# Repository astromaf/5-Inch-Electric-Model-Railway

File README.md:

# 5" Electric  Model Railway

Lovers of model railways have a wide collection of scales. One of the rarest are the 5-inch gauge. These machines are capable of taking several wagons full of visitors through an outdoor park. There are many different types, with steam being the most striking and representative.

I like to build things, and in this repository I leave useful material on the construction of my first machine, a very simple electrical model. I have done this project with my father, who is the person who has passed on my love for trains.

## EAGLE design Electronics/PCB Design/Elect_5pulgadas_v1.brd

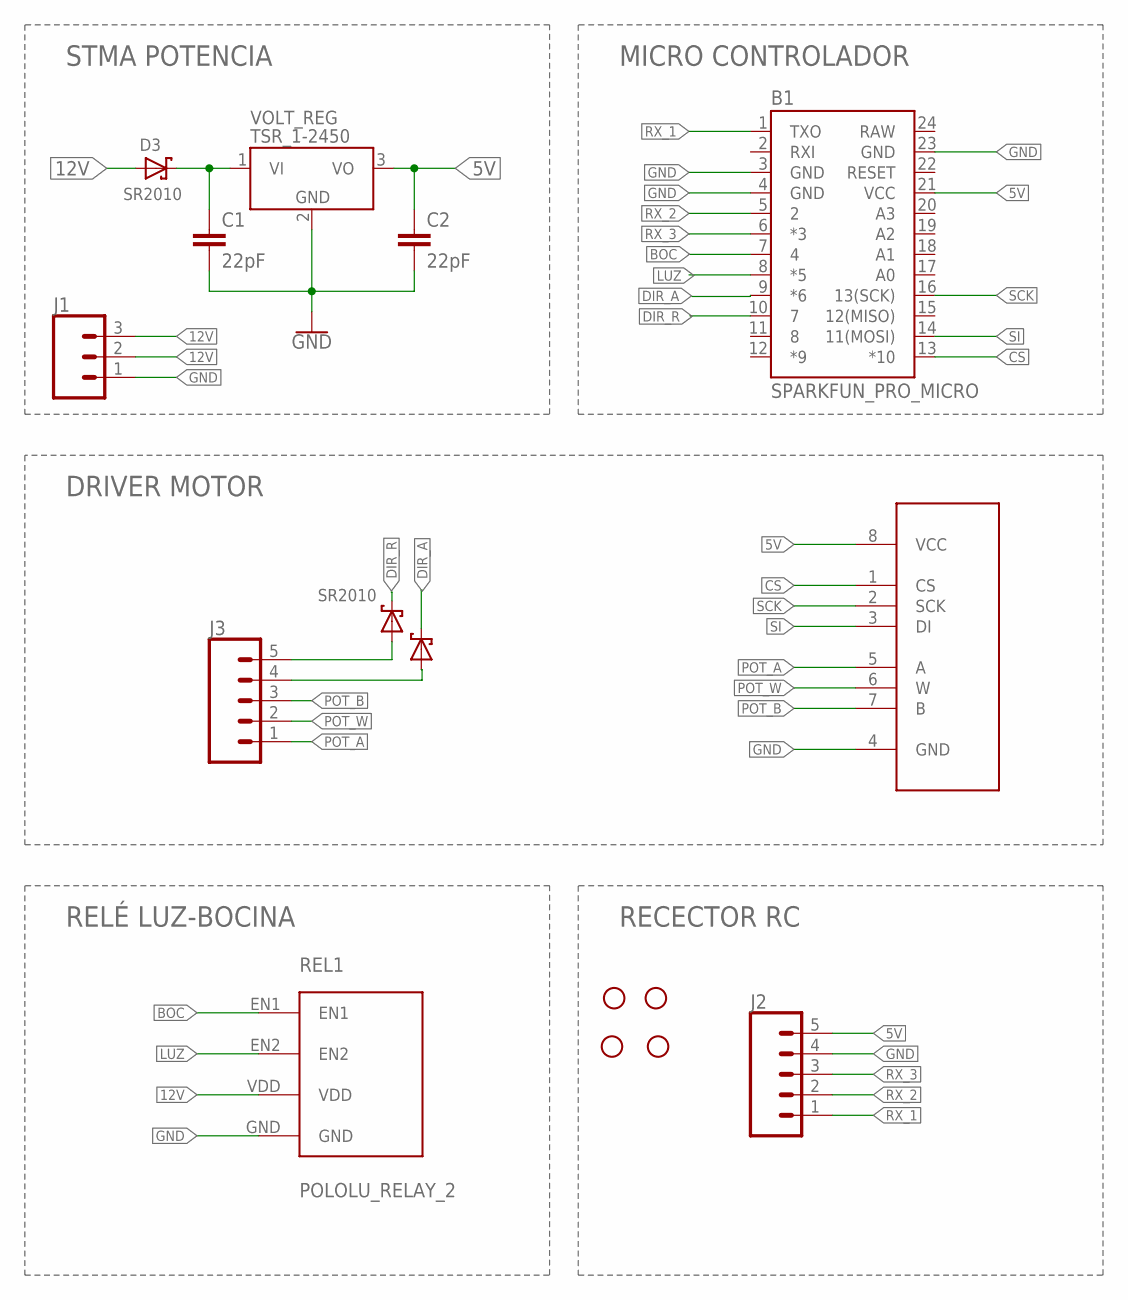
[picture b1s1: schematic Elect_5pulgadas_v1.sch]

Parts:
B1: SPARKFUN_PRO_MICRO
C1, C2: 22pF; CAP-PTH-SMALL-KIT
D1, D2, D3: SR2010; DO41-7.6
H1, H2, H3, H4: STAND-OFF
J1: CONN_03-SCREW-5MM; SCREWTERMINAL-5MM-3
J2, J3: CONN_05; 1X05
REL1: POLOLU_RELAY_2
U1: MCP41XXX; DIP08
VOLT_REG: TSR_1-2450; TSR-1

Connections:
5V: B1.21 (VCC), C2.1, J2.5, U1.8 (VCC), VOLT_REG.3 (VO)
12V: D3.A, J1.2, J1.3, REL1.VDD
BOC: B1.7 (4), REL1.EN1
CS: B1.13 (*10), U1.1 (CS)
DIR_A: B1.9 (*6), D1.C
DIR_R: B1.10 (7), D2.C
GND: B1.3 (GND), B1.4 (GND), B1.23 (GND), C1.2, C2.2, J1.1, J2.4, REL1.GND, U1.4 (GND), VOLT_REG.2 (GND)
LUZ: B1.8 (*5), REL1.EN2
unnamed: D1.A, J3.4
unnamed: D2.A, J3.5
POT_A: J3.1, U1.5 (A)
POT_B: J3.3, U1.7 (B)
POT_W: J3.2, U1.6 (W)
RAW: B1.24 (RAW)
RX_1: B1.1 (TXO), J2.1
RX_2: B1.5 (2), J2.2
RX_3: B1.6 (*3), J2.3
SCK: B1.16 (13(SCK)), U1.2 (SCK)
SI: B1.14 (11(MOSI)), U1.3 (DI)
VI: C1.1, D3.C, VOLT_REG.1 (VI)

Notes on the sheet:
STMA POTENCIA
RELÉ LUZ-BOCINA
DRIVER MOTOR
RECECTOR RC
MICRO CONTROLADOR

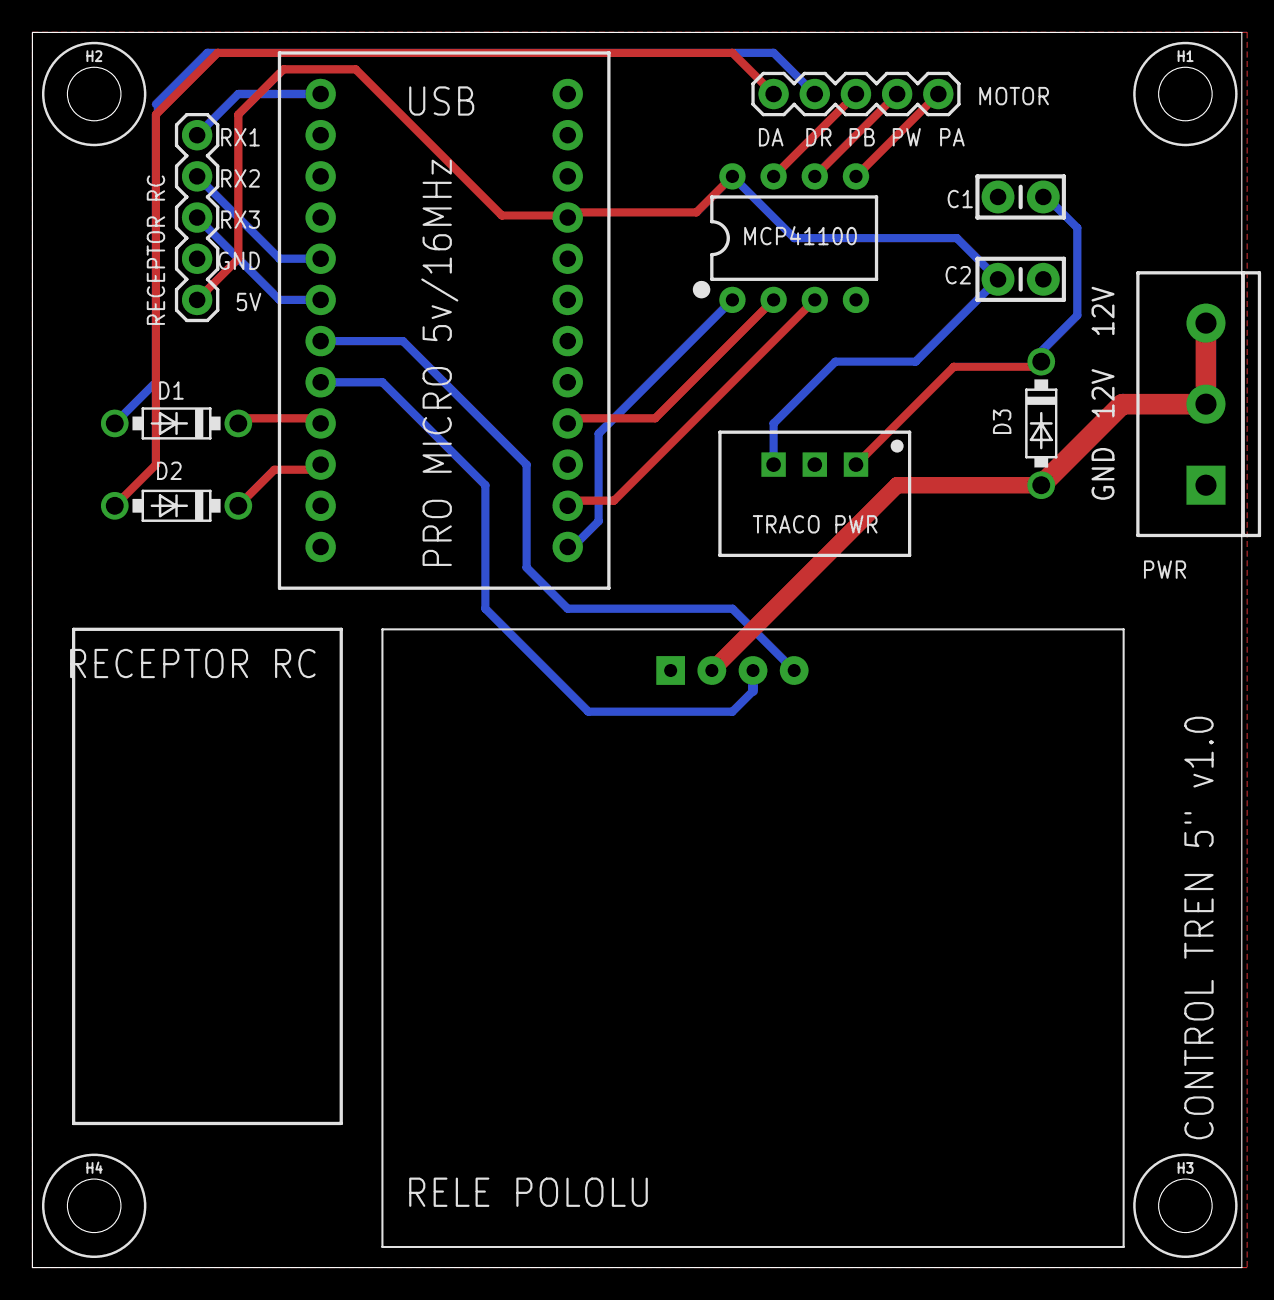
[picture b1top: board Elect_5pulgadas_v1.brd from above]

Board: 2 copper layers, 74.6 x 76.2 mm, 16 parts (0 on the bottom side), 19 nets.

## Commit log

2022-09-18 Kick-off
2022-09-18 Create Tren_Nuria.jpeg
    Tren Nuria added
2022-09-18 Video upload
    Videos
2022-09-18 Gif updated

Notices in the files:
parts and their libraries:
SparkFun-Boards: Licensing: Creative Commons ShareAlike 4.0 International - https://creativecommons.org/licenses/by-sa/4.0
